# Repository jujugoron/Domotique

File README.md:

# Domotique
Projet de box domotique (projet en cours de réalisation)

# Objectifs:
*Ce projet a pour but de mettre en oeuvre un reseau de communication Zigbee pour créer une box domotique. 
Les composants utilisés sont les suivants:

[Raspberry PI 3B](https://fr.rs-online.com/web/p/raspberry-pi/1828032/?r=f&redirect-relevancy-data=7365617263685F636173636164655F6F726465723D31267365617263685F696E746572666163655F6E616D653D4931384E525353746F636B4E756D626572267365617263685F6C616E67756167655F757365643D656E267365617263685F6D617463685F6D6F64653D6D61746368616C6C267365617263685F7061747465726E5F6D6174636865643D5E2828282872737C5253295B205D3F293F285C647B337D5B5C2D5C735D3F5C647B332C347D5B705061415D3F29297C283235285C647B387D7C5C647B317D5C2D5C647B377D29292924267365617263685F7061747465726E5F6F726465723D31267365617263685F73745F6E6F726D616C697365643D59267365617263685F726573706F6E73655F616374696F6E3D5265646972656374267365617263685F747970653D52535F53544F434B5F4E554D424552267365617263685F77696C645F63617264696E675F6D6F64653D4E4F4E45267365617263685F6B6579776F72643D3839362D38363630267365617263685F6B6579776F72645F6170703D38393638363630267365617263685F636F6E6669673D3126&searchHistory=%7B%22enabled%22%3Atrue%7D)

[Ecran tactile](https://fr.rs-online.com/web/p/ecrans-raspberry-pi/8997466/?relevancy-data=7365617263685F636173636164655F6F726465723D31267365617263685F696E746572666163655F6E616D653D4931384E525353746F636B4E756D626572267365617263685F6C616E67756167655F757365643D656E267365617263685F6D617463685F6D6F64653D6D61746368616C6C267365617263685F7061747465726E5F6D6174636865643D5E2828282872737C5253295B205D3F293F285C647B337D5B5C2D5C735D3F5C647B332C347D5B705061415D3F29297C283235285C647B387D7C5C647B317D5C2D5C647B377D29292924267365617263685F7061747465726E5F6F726465723D31267365617263685F73745F6E6F726D616C697365643D59267365617263685F726573706F6E73655F616374696F6E3D267365617263685F747970653D52535F53544F434B5F4E554D424552267365617263685F77696C645F63617264696E675F6D6F64653D4E4F4E45267365617263685F6B6579776F72643D3839392D37343636267365617263685F6B6579776F72645F6170703D38393937343636267365617263685F636F6E6669673D3126&searchHistory=%7B%22enabled%22%3Atrue%7D)

[Antenne Zigbee](https://phoscon.de/en/raspbee2/)

[Capteur de temperature]( https://expo.tuya.com/product/712038)

[Prise connectée]( https://www.batna24.com/en/p/xiaomi-mi-smart-plug-zigbee-wall-plug-rmmmh#support)

## Hardware
Installation de l'ecran et de la RPI 
installation du capteur Zigbee
### Electronique
relier l'ecran et l'antenne Raspbee sur la Raspberry PI. (utiliser la carte kicad si besoin)

### Support
un modèle fusion 360 est disponible dans le dossier Hardware. Il est inspiré du modèle [thingiverse]( https://www.thingiverse.com/thing:2756684 )

le modèle a été imprimé en PLA et TPU avec une Creality CR10

## Software
###installer Raspbian sur la RPI

### Mettre à jour

```
sudo apt update
sudo apt upgrade
```

### Installation de deCONZ et de la puce RaspBee

#### Désactivation de la console Serie 

```
sudo raspi-config
```
Advanced Options -> Serial -> Disable Commandline over Serial

#### Désactivation du service getty
```
sudo systemctl disable serial-getty@ttyAMA0.service
```
#### Désactivation du bluetooth 

1. Ajouter la ligne suivant dans le fichier /boot/config.txt:
```
sudo nano /boot/config.txt
```
```
dtoverlay=pi3-disable-bt
```
2. Désactivation du modem Bluetooth
```
sudo systemctl disable hciuart
```
#### Installation de l'application DeCONZ
```
sudo gpasswd -a $USER dialout
wget -O - http://phoscon.de/apt/deconz.pub.key | sudo apt-key add -
sudo sh -c "echo 'deb http://phoscon.de/apt/deconz $(lsb_release -cs) main' > /etc/apt/sources.list.d/deconz.list"
sudo apt update
sudo apt install deconz
sudo systemctl edit deconz-gui
```

ajouter l'option

```
–ws-port=8081
```

#### Lancement de l'application
```
sudo systemctl disable deconz
sudo systemctl stop deconz
sudo systemctl enable deconz-gui
```

#### Redémarrage
```
sudo reboot
```

[Tuto]( https://presentationdeconz.wordpress.com/installation/)

### Installation d'Apache2
```
sudo apt install apache2 -y
```
```
sudo chown -R pi:www-data /var/www/html/
sudo chmod -R 770 /var/www/html/
```

###Installation de PHP

```
sudo apt install php -y

sudo service apache2 restart

```

### placer les fichiers de l'application Web "Software" dans le dossier /var/www/html 

```
sudo cp -r /home/pi/Desktop/Software /var/www/html
```

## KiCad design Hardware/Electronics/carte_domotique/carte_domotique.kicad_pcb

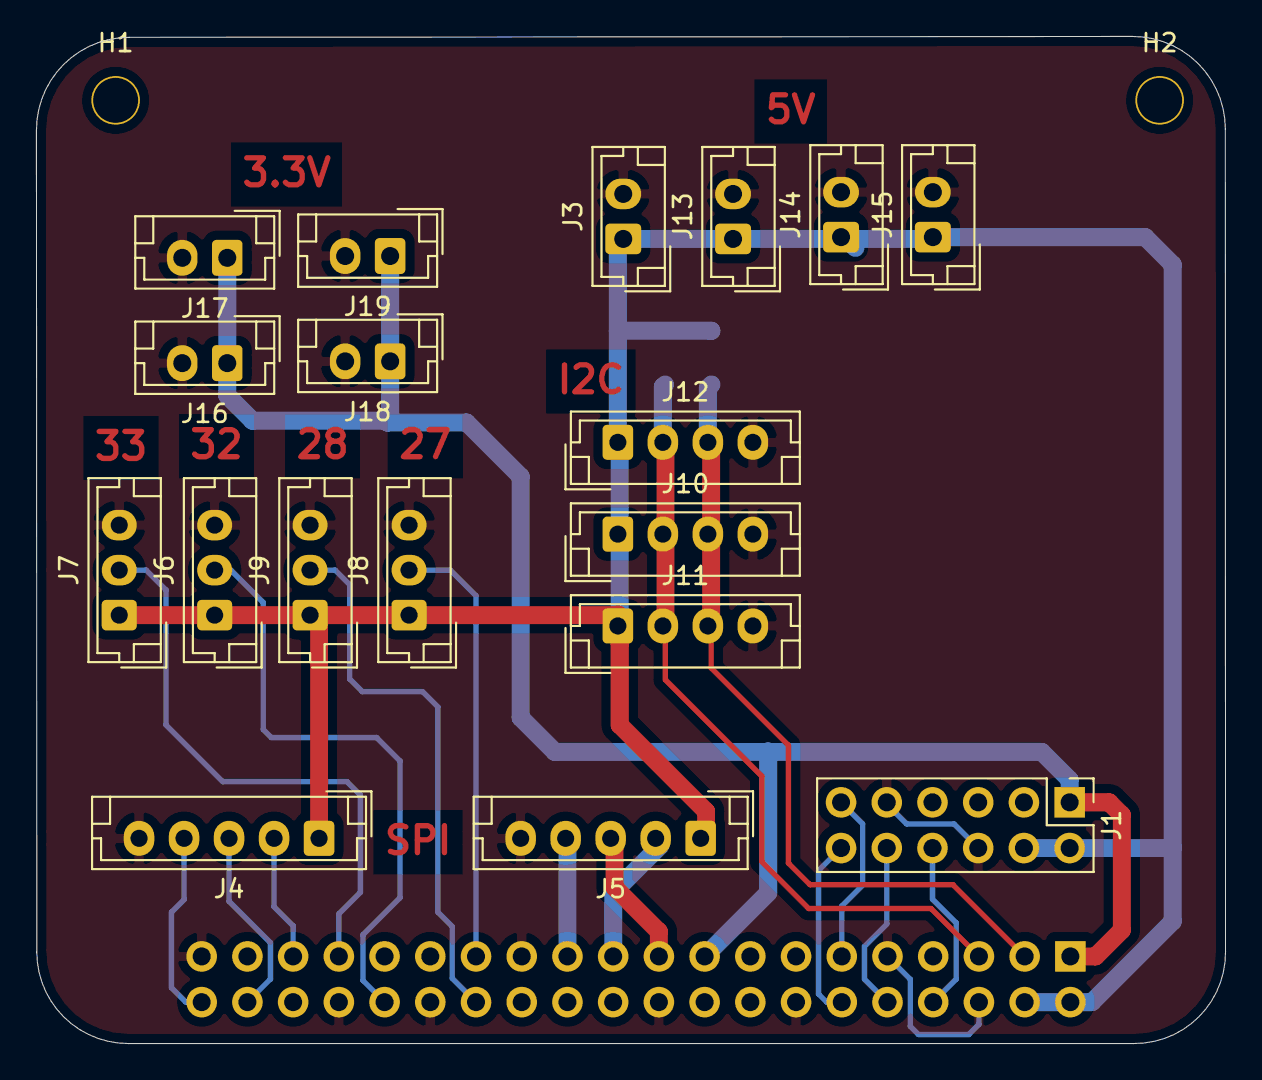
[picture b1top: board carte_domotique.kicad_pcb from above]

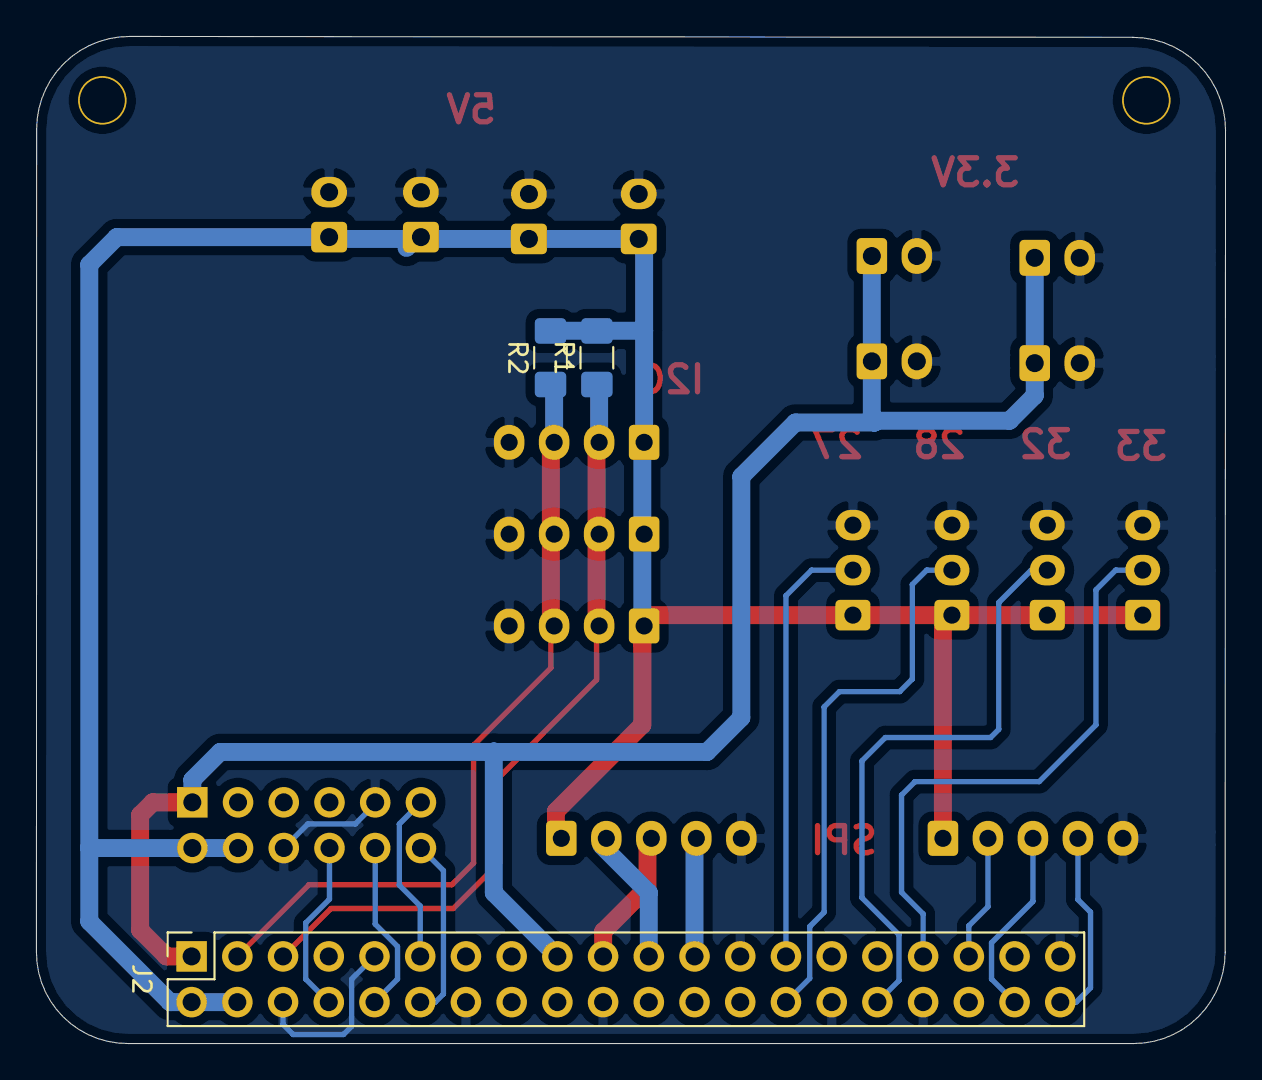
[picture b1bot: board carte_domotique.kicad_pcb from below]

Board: 2 copper layers, 66.1 x 55.9 mm, 23 parts (3 on the bottom side), 19 nets.

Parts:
H1, H2: MountingHole_Pad; MountingHole_2.2mm_M2
J1: Conn_02x06_Odd_Even; PinHeader_2x06_P2.54mm_Vertical
J2: Raspberry_Pi_2_3; PinSocket_2x20_P2.54mm_Vertical
J3, J13, J14, J15, J16, J17, J18, J19: Conn_01x02; JST_EH_B2B-EH-A_1x02_P2.50mm_Vertical
J4, J5: Conn_01x05; JST_EH_B5B-EH-A_1x05_P2.50mm_Vertical
J6, J7, J8, J9: Conn_01x03; JST_EH_B3B-EH-A_1x03_P2.50mm_Vertical
J10, J11, J12: Conn_01x04; JST_EH_B4B-EH-A_1x04_P2.50mm_Vertical
R1, R2: R; R_1206_3216Metric_Pad1.42x1.75mm_HandSolder

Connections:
+3V3: J1.1, J2.1, J2.17, J16.1, J17.1, J18.1, J19.1
+5V: J1.2, J1.4, J2.2, J2.4, J3.1, J4.1, J5.1, J6.1, J7.1, J8.1, J9.1, J10.1, J11.1, J12.1, J13.1, J14.1, J15.1, R1.2, R2.2
/SW1: J1.12, J2.12
GND: J1.6, J1.9, J2.6, J2.9, J2.14, J2.20, J2.25, J2.30, J2.34, J2.39, J3.2, J4.5, J5.5, J6.3, J7.3, J8.3, J9.3, J10.4, J11.4, J12.4, J13.2, J14.2, J15.2, J16.2, J17.2, J18.2, J19.2
unnamed: J1.8, J2.8
unnamed: J1.10, J2.10
unnamed: J2.19, J5.3
unnamed: J2.21, J5.2
unnamed: J2.23, J5.4
unnamed: J2.27, J8.2
unnamed: J2.28, J9.2
unnamed: J2.32, J6.2
unnamed: J2.33, J7.2
unnamed: J2.35, J4.2
unnamed: J2.38, J4.3
unnamed: J2.40, J4.4
SCL: J2.5, J10.2, J11.2, J12.2, R1.1
SDA: J2.3, J10.3, J11.3, J12.3, R2.1
reset: J1.11, J2.11

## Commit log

2021-10-20 update readme et partitionnement du dossier
    update readme
    partitionnement du dossier (hard/soft)
    test github
2021-10-20 creation fichier kicad carte
2021-11-02 debut de la carte electronique
2021-11-02 update readme
    test avec les ```
2021-11-02 Update README.md
    création du cadre de code
2021-11-04 motification du conneteur pour le raspbee II
2021-11-04 kicad+ doc
    ajout de document
    modification avec le cablage de l'antenne xbee d'après la datasheet
2021-11-04 kicad
    schematic + empreinte
    tracage des bus
    + mise en place des connecteur spi i2c pwm pcm 5v 33v gnd
2021-11-05 Update README.md
    ajout du tuto d'installation de Deconz
2021-12-17 carte 1
    carte proto 1
2022-01-04 carte electronique
    finalisation de la carte électronique
    + exportation 3D
2022-01-04 conception3D
    ajout de l'assemblage de base
2022-01-31 Update README.md
    ajout installation Apache2 + PHP+ para de deconz
2022-01-31 Update README.md
    commande pour l'installation du programme
2022-01-31 Update README.md
    ajout hardware
2022-02-05 maj chemin
2022-02-05 chemin
2022-02-07 droit modification fichiers apache
2022-02-10 hardware
2022-02-10 soft
2022-02-10 maj code
2022-02-10 fin du code
2022-02-16 fin projet
